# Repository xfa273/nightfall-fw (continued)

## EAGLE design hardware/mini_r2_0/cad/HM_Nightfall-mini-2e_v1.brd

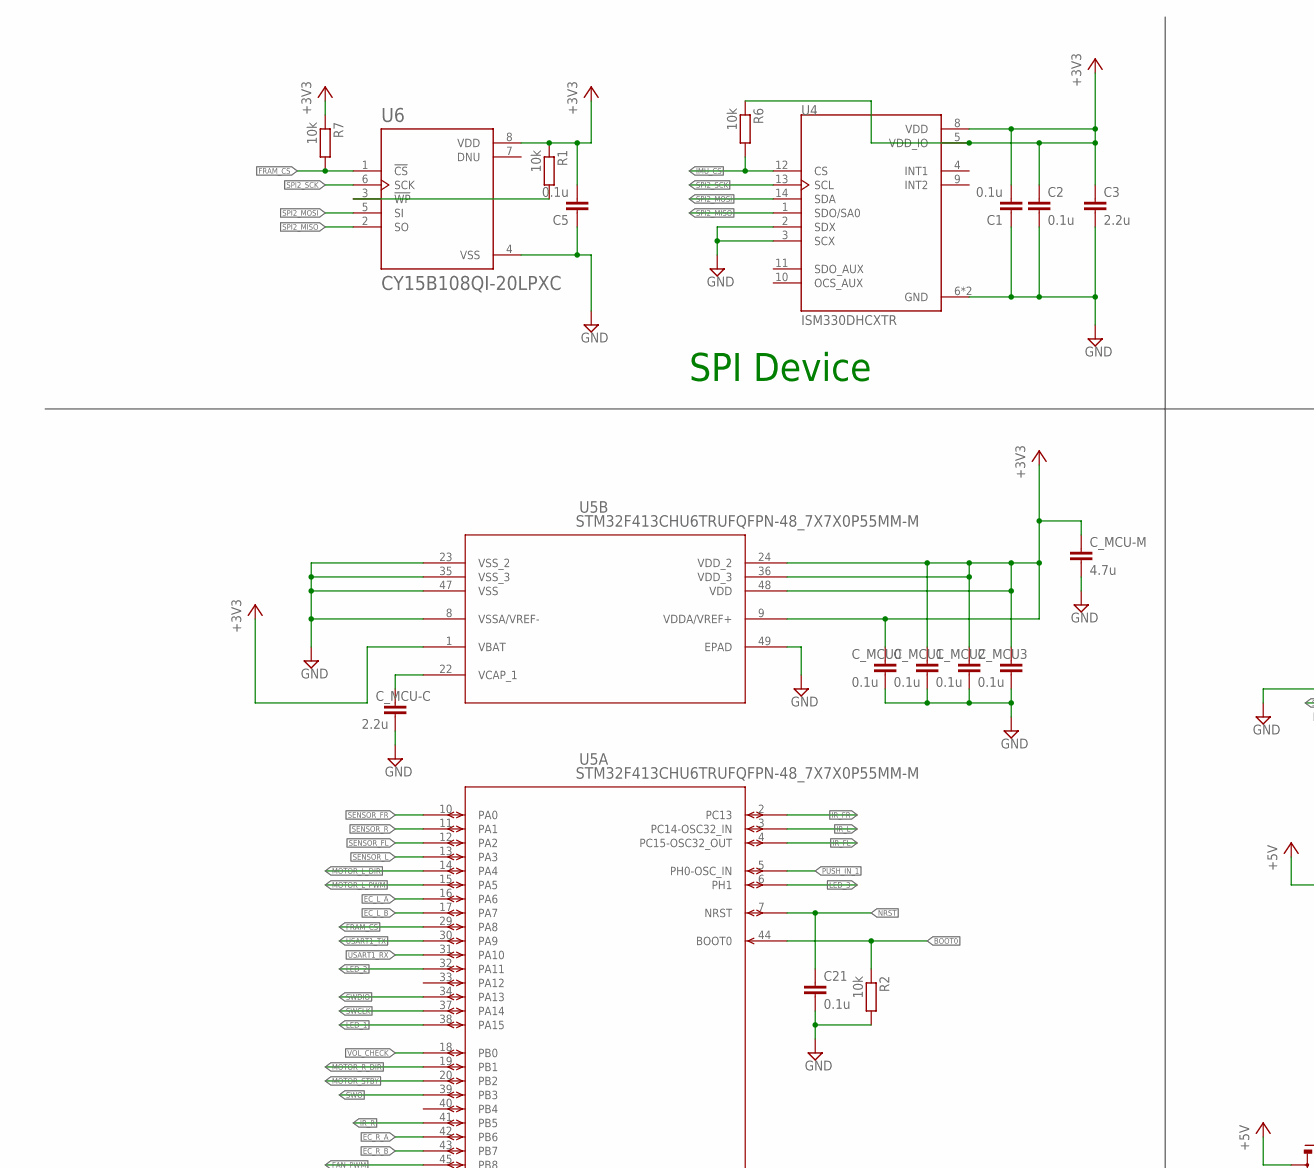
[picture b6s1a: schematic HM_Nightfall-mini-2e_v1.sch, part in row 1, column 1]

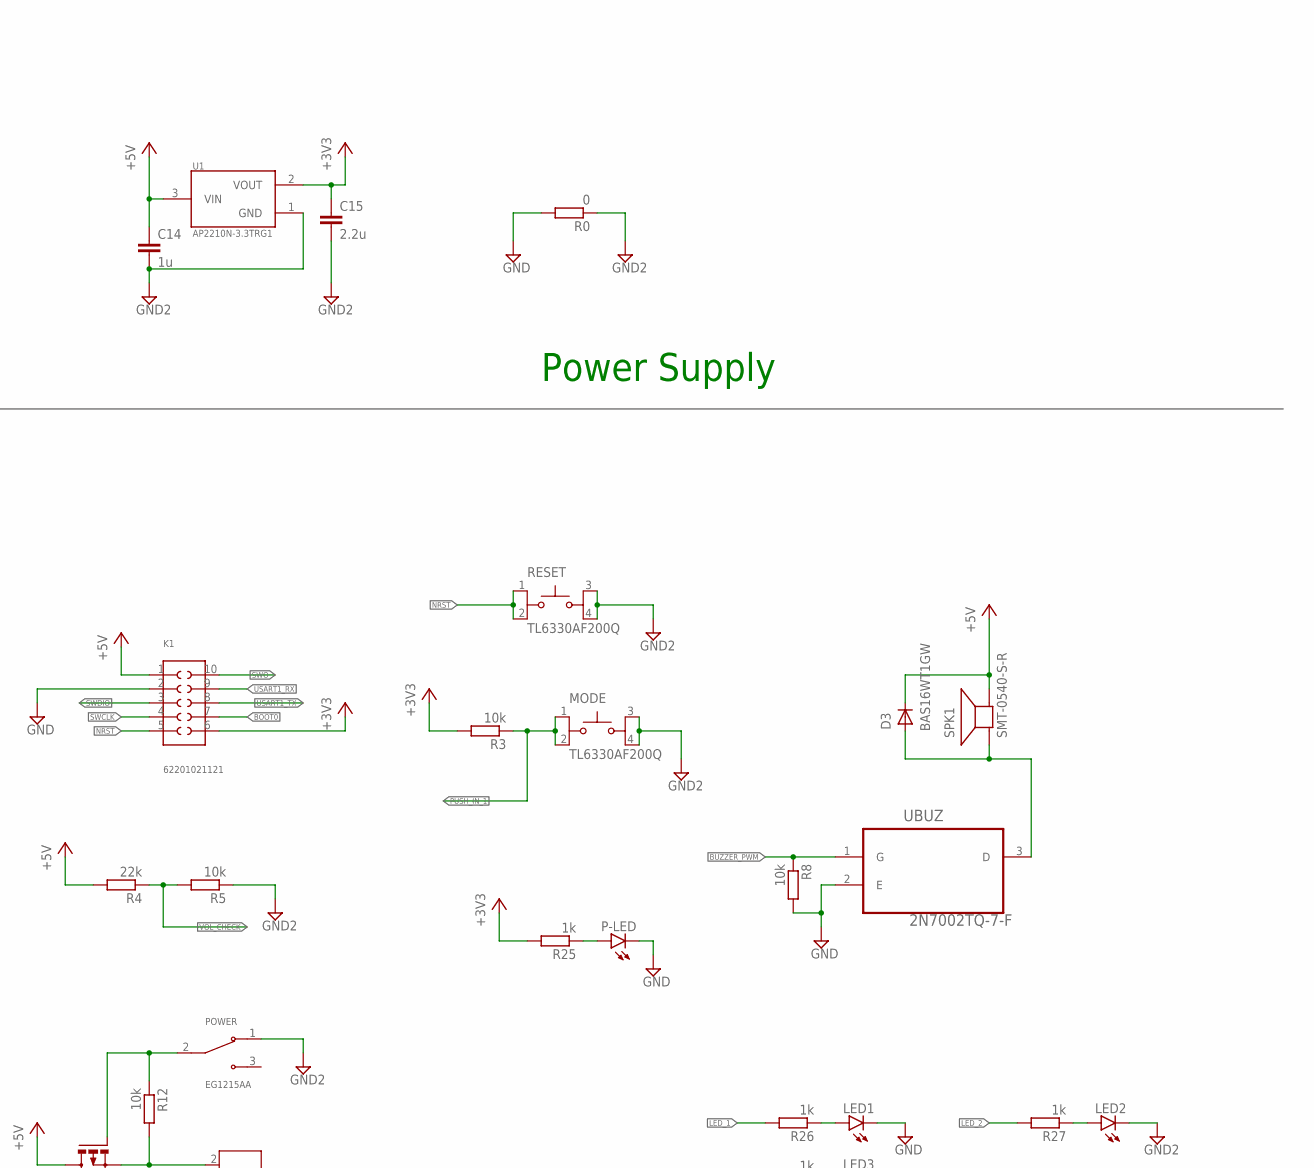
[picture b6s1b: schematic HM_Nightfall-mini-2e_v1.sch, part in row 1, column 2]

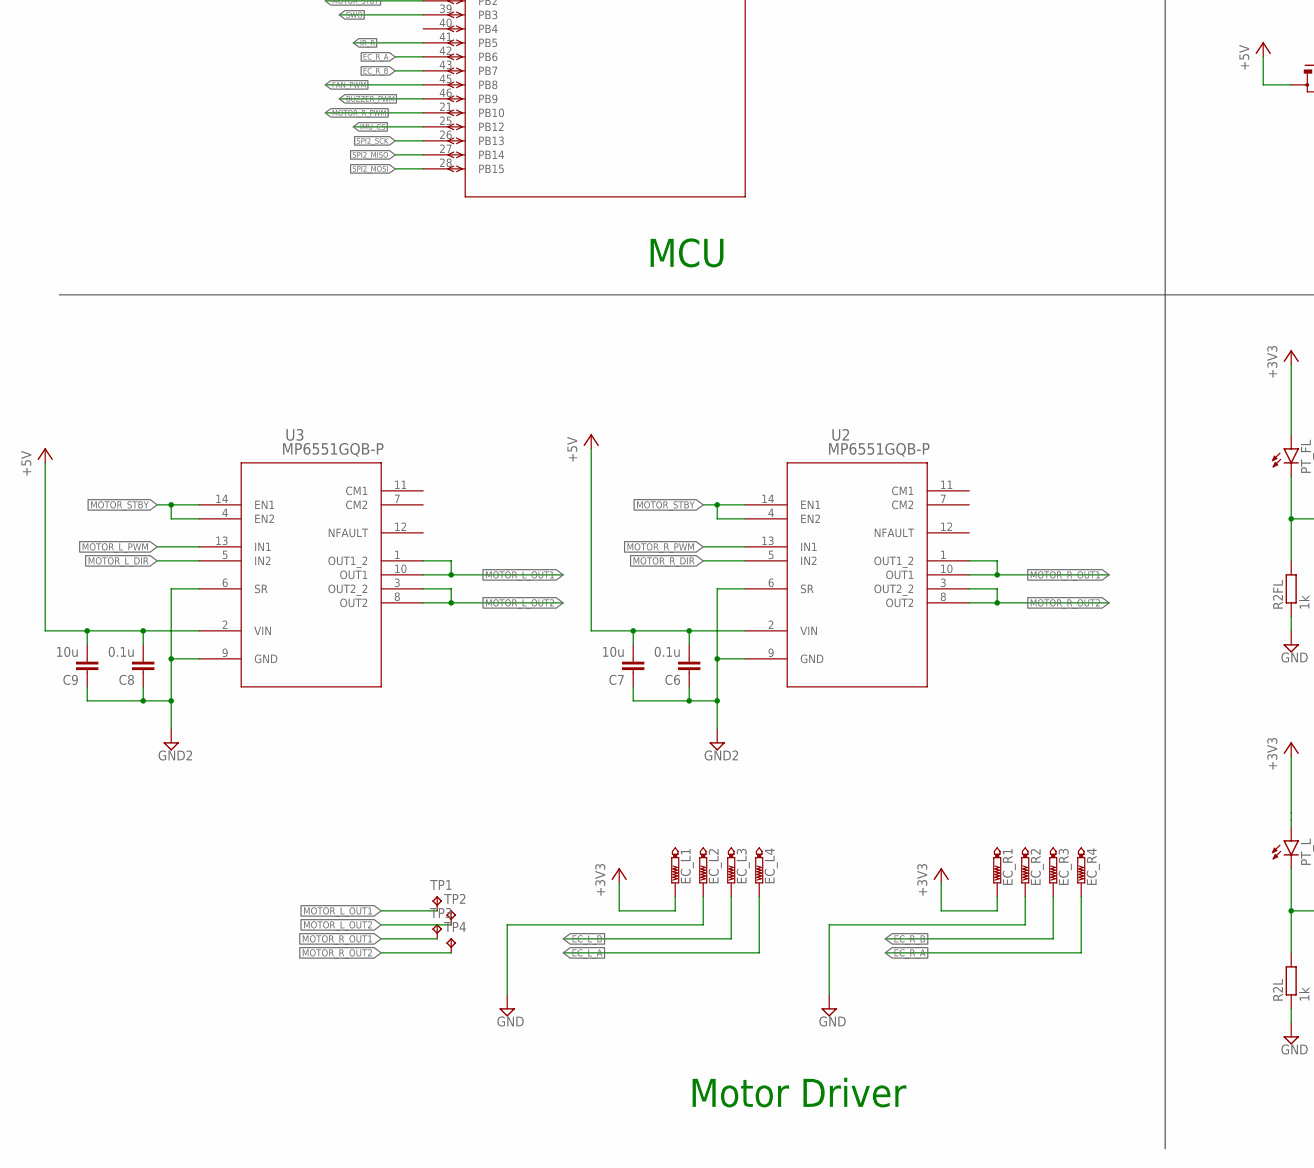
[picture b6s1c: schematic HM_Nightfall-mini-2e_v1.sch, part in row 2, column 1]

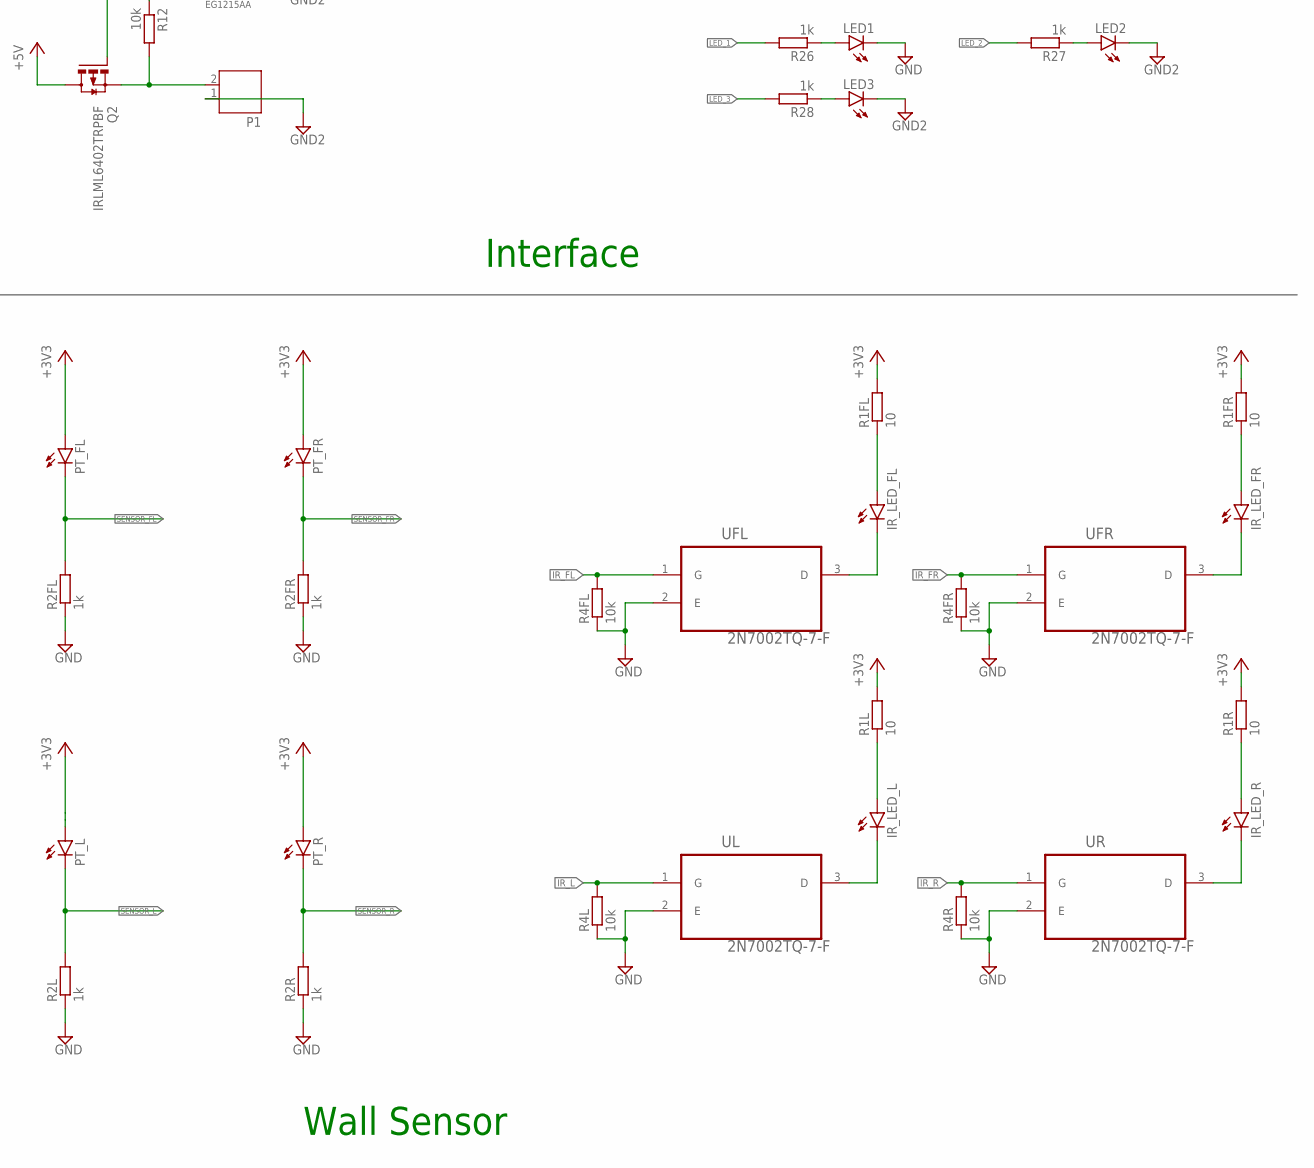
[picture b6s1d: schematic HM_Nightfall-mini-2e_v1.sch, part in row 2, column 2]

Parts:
C1, C2, C5, C6, C8, C21: 0.1u; C0402
C3, C15: 2.2u; C0402
C7, C9: 10u; C0402
C14: 1u; C0402
C_MCU0, C_MCU1, C_MCU2, C_MCU3: 0.1u; C0402
C_MCU-C: 2.2u; C0402
C_MCU-M: 4.7u; C0402
D3: BAS16WT1GW; SOT323
EC_L1, EC_L2, EC_L3, EC_L4: PTR1TP06SQ; TP06SQ
EC_R1, EC_R2, EC_R3, EC_R4: PTR1TP06SQ; TP06SQ
IR_LED_FL: LED3MM
IR_LED_FR: LED3MM
IR_LED_L: LED3MM
IR_LED_R: LED3MM
K1: 62201021121
LED1, LED2, LED3: LEDCHIPLED_0603; CHIPLED_0603
MODE: TL6330AF200Q; SW_TL6330AF200Q
P1: JST-PH2
P-LED: LEDCHIPLED_0603; CHIPLED_0603
POWER: EG1215AA; SW_EG1215AA
PT_FL: LED3MM
PT_FR: LED3MM
PT_L: LED3MM
PT_R: LED3MM
Q2: IRLML6402TRPBF; SOT23
R0: 0; R0402
R1, R2, R3, R4FL, R4FR, R4L, R4R, R5, R6, R7, R8, R12: 10k; R0402
R1FL, R1FR, R1L, R1R: 10; R0402
R2FL, R2FR, R2L, R2R, R25, R26, R27, R28: 1k; R0402
R4: 22k; R0402
RESET: TL6330AF200Q; SW_TL6330AF200Q
SPK1: SMT-0540-S-R
TP1, TP2, TP3, TP4: TPB1,27; B1,27
U1: AP2210N-3.3TRG1; SOT95P280X145-3N
U2, U3: MP6551GQB-P; QFN-14_MP6551_MNP
U4: ISM330DHCXTR; PQFN50P250X300X86-14N
U5: STM32F413CHU6TRUFQFPN-48_7X7X0P55MM-M; UFQFPN-48_7X7X0P55MM-M
U6: CY15B108QI-20LPXC; SON65P328X323X55-8N
UBUZ: 2N7002TQ-7-F; SOT50P160X90-3N
UFL: 2N7002TQ-7-F; SOT50P160X90-3N
UFR: 2N7002TQ-7-F; SOT50P160X90-3N
UL: 2N7002TQ-7-F; SOT50P160X90-3N
UR: 2N7002TQ-7-F; SOT50P160X90-3N

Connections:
+3V3: C1.2, C2.1, C3.1, C5.2, C15.1, C_MCU0.1, C_MCU1.1, C_MCU2.1, C_MCU3.1, C_MCU-M.1, EC_L1.TP, EC_R1.TP, K1.6, PT_FL.A, PT_FR.A, PT_L.A, PT_R.A, R1.1, R1FL.2, R1FR.2, R1L.2, R1R.2, R3.2, R6.1, R7.1, R25.2, U1.2 (VOUT), U4.5 (VDD_IO), U4.8 (VDD), U5.1 (VBAT), U5.9 (VDDA/VREF+), U5.24 (VDD_2), U5.36 (VDD_3), U5.48 (VDD), U6.8 (VDD)
+5V: C6.2, C7.2, C8.2, C9.2, C14.1, D3.3 (K), K1.1, Q2.3 (D), R4.2, SPK1.+ (-), U1.3 (VIN), U2.2 (VIN), U3.2 (VIN)
BOOT0: K1.7, R2.1, U5.44 (BOOT0)
BUZZER_PWM: R8.1, U5.46 (PB9), UBUZ.1 (G)
EC_L_A: EC_L4.TP, U5.16 (PA6)
EC_L_B: EC_L3.TP, U5.17 (PA7)
EC_R_A: EC_R4.TP, U5.42 (PB6)
EC_R_B: EC_R3.TP, U5.43 (PB7)
FAN_PWM: U5.45 (PB8)
FRAM_CS: R7.2, U5.29 (PA8), U6.1 (!CS)
GND: C1.1, C2.2, C3.2, C5.1, C21.2, C_MCU0.2, C_MCU1.2, C_MCU2.2, C_MCU3.2, C_MCU-C.2, C_MCU-M.2, EC_L2.TP, EC_R2.TP, K1.2, LED1.C, P-LED.C, R0.2, R2.2, R2FL.1, R2FR.1, R2L.1, R2R.1, R4FL.1, R4FR.1, R4L.1, R4R.1, R8.2, U4.2 (SDX), U4.3 (SCX), U4.6 (GND), U4.7 (GND), U5.8 (VSSA/VREF-), U5.23 (VSS_2), U5.35 (VSS_3), U5.47 (VSS), U5.49 (EPAD), U6.4 (VSS), UBUZ.2 (E), UFL.2 (E), UFR.2 (E), UL.2 (E), UR.2 (E)
GND2: C6.1, C7.1, C8.1, C9.1, C14.2, C15.2, LED2.C, LED3.C, MODE.3, MODE.4, P1.1, POWER.1, R0.1, R5.1, RESET.3, RESET.4, U1.1 (GND), U2.6 (SR), U2.9 (GND), U3.6 (SR), U3.9 (GND)
IMU_CS: R6.2, U4.12 (CS), U5.25 (PB12)
IR_FL: R4FL.2, U5.4 (PC15-OSC32_OUT), UFL.1 (G)
IR_FR: R4FR.2, U5.2 (PC13), UFR.1 (G)
IR_L: R4L.2, U5.3 (PC14-OSC32_IN), UL.1 (G)
IR_R: R4R.2, U5.41 (PB5), UR.1 (G)
LED_1: R26.2, U5.38 (PA15)
LED_2: R27.2, U5.32 (PA11)
LED_3: R28.2, U5.6 (PH1)
MOTOR_L_DIR: U3.5 (IN2), U5.14 (PA4)
MOTOR_L_OUT1: TP1.TP, U3.1 (OUT1_2), U3.10 (OUT1)
MOTOR_L_OUT2: TP2.TP, U3.3 (OUT2_2), U3.8 (OUT2)
MOTOR_L_PWM: U3.13 (IN1), U5.15 (PA5)
MOTOR_R_DIR: U2.5 (IN2), U5.19 (PB1)
MOTOR_R_OUT1: TP3.TP, U2.1 (OUT1_2), U2.10 (OUT1)
MOTOR_R_OUT2: TP4.TP, U2.3 (OUT2_2), U2.8 (OUT2)
MOTOR_R_PWM: U2.13 (IN1), U5.21 (PB10)
MOTOR_STBY: U2.4 (EN2), U2.14 (EN1), U3.4 (EN2), U3.14 (EN1), U5.20 (PB2)
unnamed: IR_LED_FL.K (C), UFL.3 (D)
unnamed: R1.2, U6.3 (!WP)
unnamed: C_MCU-C.1, U5.22 (VCAP_1)
unnamed: P1.2, Q2.2 (S), R12.2
unnamed: IR_LED_FL.A, R1FL.1
unnamed: IR_LED_L.K (C), UL.3 (D)
unnamed: POWER.2, Q2.1 (G), R12.1
unnamed: IR_LED_L.A, R1L.1
unnamed: IR_LED_FR.K (C), UFR.3 (D)
unnamed: P-LED.A, R25.1
unnamed: D3.1 (A), SPK1.- (+), UBUZ.3 (D)
unnamed: LED1.A, R26.1
unnamed: IR_LED_FR.A, R1FR.1
unnamed: IR_LED_R.K (C), UR.3 (D)
unnamed: IR_LED_R.A, R1R.1
unnamed: LED2.A, R27.1
unnamed: LED3.A, R28.1
NRST: C21.1, K1.5, RESET.1, RESET.2, U5.7 (NRST)
PUSH_IN_1: MODE.1, MODE.2, R3.1, U5.5 (PH0-OSC_IN)
SENSOR_FL: PT_FL.K (C), R2FL.2, U5.12 (PA2)
SENSOR_FR: PT_FR.K (C), R2FR.2, U5.10 (PA0)
SENSOR_L: PT_L.K (C), R2L.2, U5.13 (PA3)
SENSOR_R: PT_R.K (C), R2R.2, U5.11 (PA1)
SPI2_MISO: U4.1 (SDO/SA0), U5.27 (PB14), U6.2 (SO)
SPI2_MOSI: U4.14 (SDA), U5.28 (PB15), U6.5 (SI)
SPI2_SCK: U4.13 (SCL), U5.26 (PB13), U6.6 (SCK)
SWCLK: K1.4, U5.37 (PA14)
SWDIO: K1.3, U5.34 (PA13)
SWO: K1.10, U5.39 (PB3)
USART1_RX: K1.9, U5.31 (PA10)
USART1_TX: K1.8, U5.30 (PA9)
VOL_CHECK: R4.1, R5.2, U5.18 (PB0)

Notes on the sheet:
Power Supply
MCU
Interface
Motor Driver
Wall Sensor
SPI Device

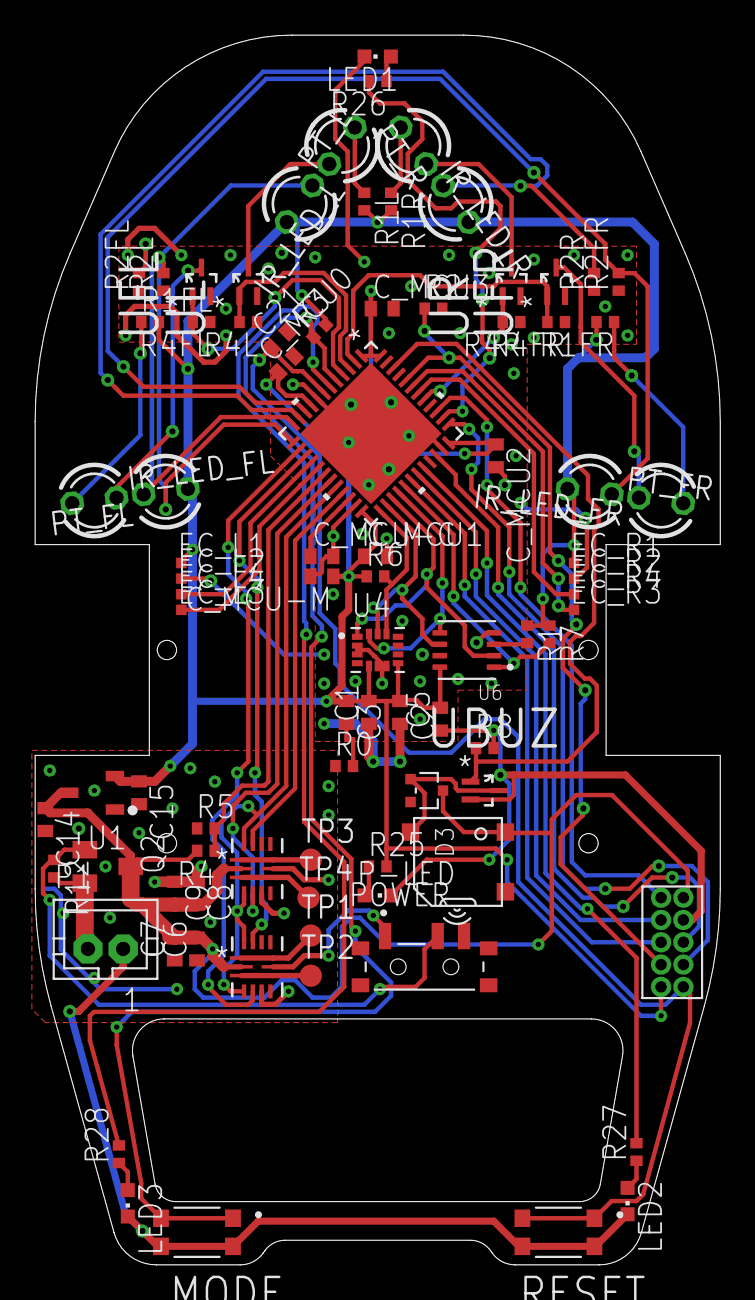
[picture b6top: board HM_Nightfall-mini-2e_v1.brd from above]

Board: 2 copper layers, 39.0 x 70.0 mm, 86 parts (0 on the bottom side), 60 nets.

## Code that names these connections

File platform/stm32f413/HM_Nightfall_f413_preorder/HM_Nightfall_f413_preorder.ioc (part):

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Mcu.Name=STM32F413C(G-H)Ux
Mcu.Package=UFQFPN48
Mcu.UserName=STM32F413CHUx
PA0.GPIOParameters=GPIO_Label
PA0.GPIO_Label=SENSOR_FR
PA0.Signal=ADCx_IN0
PA1.GPIOParameters=GPIO_Label
PA1.GPIO_Label=SENSOR_R
PA1.Signal=ADCx_IN1
PA10.Mode=Asynchronous
PA10.Signal=USART1_RX
PA11.GPIOParameters=GPIO_Label
PA11.GPIO_Label=LED_2
PA11.Signal=GPIO_Output
PA13.Mode=Trace_Asynchronous_SW
PA13.Signal=SYS_JTMS-SWDIO
PA14.Mode=Trace_Asynchronous_SW
PA14.Signal=SYS_JTCK-SWCLK
PA15.GPIOParameters=GPIO_Label
PA15.GPIO_Label=LED_1
PA15.Signal=GPIO_Output
PA2.GPIOParameters=GPIO_Label
PA2.GPIO_Label=SENSOR_FL
PA2.Signal=ADCx_IN2
PA3.GPIOParameters=GPIO_Label
PA3.GPIO_Label=SENSOR_L
PA3.Signal=ADCx_IN3
PA4.GPIOParameters=GPIO_Label
PA4.GPIO_Label=MOTOR_L_DIR
PA4.Signal=GPIO_Output
PA5.GPIOParameters=GPIO_Label
PA5.GPIO_Label=MOTOR_L_PWM
PA5.Signal=S_TIM2_CH1_ETR
PA6.GPIOParameters=GPIO_Label
PA6.GPIO_Label=EC_L_A
PA6.Signal=S_TIM3_CH1
PA7.GPIOParameters=GPIO_Label
PA7.GPIO_Label=EC_L_B
PA7.Signal=S_TIM3_CH2
PA8.GPIOParameters=GPIO_Label
PA8.GPIO_Label=FRAM_CS
PA8.Signal=GPIO_Output
PA9.Mode=Asynchronous
PA9.Signal=USART1_TX
PB0.GPIOParameters=GPIO_Label
PB0.GPIO_Label=VOL_CHECK
PB0.Signal=ADCx_IN8
PB1.GPIOParameters=GPIO_Label
PB1.GPIO_Label=MOTOR_R_DIR
PB1.Signal=GPIO_Output
PB10.GPIOParameters=GPIO_Label
PB10.GPIO_Label=MOTOR_R_PWM
PB10.Signal=S_TIM2_CH3
PB12.GPIOParameters=GPIO_Label
PB12.GPIO_Label=IMU_CS
PB12.Signal=GPIO_Output
PB13.Mode=Full_Duplex_Master
PB13.Signal=SPI2_SCK
PB14.Mode=Full_Duplex_Master
PB14.Signal=SPI2_MISO
PB15.Mode=Full_Duplex_Master
PB15.Signal=SPI2_MOSI
PB2.GPIOParameters=GPIO_Label
PB2.GPIO_Label=MOTOR_STBY
PB2.Signal=GPIO_Output
PB3.Mode=Trace_Asynchronous_SW
PB3.Signal=SYS_JTDO-SWO
PB5.GPIOParameters=GPIO_Label
PB5.GPIO_Label=IR_R
PB5.Signal=GPIO_Output
PB6.GPIOParameters=GPIO_Label
PB6.GPIO_Label=EC_R_A
PB6.Signal=S_TIM4_CH1
PB7.GPIOParameters=GPIO_Label
PB7.GPIO_Label=EC_R_B
PB7.Signal=S_TIM4_CH2
PB8.GPIOParameters=GPIO_Label
PB8.GPIO_Label=FAN_PWM
PB8.Signal=S_TIM10_CH1
PB9.GPIOParameters=GPIO_Label
PB9.GPIO_Label=BUZZER_PWM
PB9.Signal=S_TIM11_CH1
PC13.GPIOParameters=GPIO_Label
PC13.GPIO_Label=IR_FR
PC13.Signal=GPIO_Output
PC14-OSC32_IN.GPIOParameters=GPIO_Label
PC14-OSC32_IN.GPIO_Label=IR_L
PC14-OSC32_IN.Signal=GPIO_Output
PC15-OSC32_OUT.GPIOParameters=GPIO_Label
PC15-OSC32_OUT.GPIO_Label=IR_FL
PC15-OSC32_OUT.Signal=GPIO_Output
PH0\ -\ OSC_IN.GPIOParameters=GPIO_Label
PH0\ -\ OSC_IN.GPIO_Label=PUSH_IN_1
PH0\ -\ OSC_IN.Signal=GPIO_Input
PH1\ -\ OSC_OUT.GPIOParameters=GPIO_Label
PH1\ -\ OSC_OUT.GPIO_Label=LED_3
PH1\ -\ OSC_OUT.Signal=GPIO_Output
RCC.SYSCLKFreq_VALUE=100000000
RCC.SYSCLKSource=RCC_SYSCLKSOURCE_PLLCLK
board=custom

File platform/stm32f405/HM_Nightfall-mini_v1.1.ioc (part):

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Mcu.Name=STM32F405RGTx
Mcu.Package=LQFP64
Mcu.UserName=STM32F405RGTx
PA0-WKUP.GPIOParameters=GPIO_Label
PA0-WKUP.GPIO_Label=SENSOR_FR
PA0-WKUP.Signal=ADCx_IN0
PA1.GPIOParameters=GPIO_Label
PA1.GPIO_Label=SENSOR_R
PA1.Signal=ADCx_IN1
PA10.GPIOParameters=GPIO_Label
PA10.GPIO_Label=PC_TX
PA10.Mode=Asynchronous
PA10.Signal=USART1_RX
PA12.GPIOParameters=GPIO_PuPd,GPIO_Label
PA12.GPIO_Label=IR_FR
PA12.GPIO_PuPd=GPIO_PULLDOWN
PA12.Signal=GPIO_Output
PA13.GPIOParameters=GPIO_Label
PA13.GPIO_Label=SWDIO
PA13.Signal=SYS_JTMS-SWDIO
PA14.GPIOParameters=GPIO_Label
PA14.GPIO_Label=SWCL
PA14.Signal=SYS_JTCK-SWCLK
PA15.GPIOParameters=GPIO_Label
PA15.GPIO_Label=LED_1
PA15.Signal=GPIO_Output
PA2.GPIOParameters=GPIO_Label
PA2.GPIO_Label=SENSOR_FL
PA2.Signal=ADCx_IN2
PA3.GPIOParameters=GPIO_Label
PA3.GPIO_Label=SENSOR_L
PA3.Signal=ADCx_IN3
PA5.GPIOParameters=GPIO_Label
PA5.GPIO_Label=MOTOR_L_PWM
PA5.Signal=S_TIM2_CH1_ETR
PA7.GPIOParameters=GPIO_Label
PA7.GPIO_Label=MOTOR_L_DIR
PA7.Signal=GPIO_Output
PA8.GPIOParameters=GPIO_Label
PA8.GPIO_Label=SCL
PA8.Signal=I2C3_SCL
PA9.GPIOParameters=GPIO_Label
PA9.GPIO_Label=PC_RX
PA9.Mode=Asynchronous
PA9.Signal=USART1_TX
PB10.GPIOParameters=GPIO_Label
PB10.GPIO_Label=MOTOR_R_DIR
PB10.Signal=GPIO_Output
PB11.GPIOParameters=GPIO_Label
PB11.GPIO_Label=MOTOR_R_PWM
PB11.Signal=S_TIM2_CH4
PB15.GPIOParameters=GPIO_Label
PB15.GPIO_Label=LED_2
PB15.Signal=GPIO_Output
PB4.GPIOParameters=GPIO_Label
PB4.GPIO_Label=FAN
PB4.Signal=S_TIM3_CH1
PB5.GPIOParameters=GPIO_Label
PB5.GPIO_Label=BUZZER
PB5.Signal=S_TIM3_CH2
PB6.GPIOParameters=GPIO_Label
PB6.GPIO_Label=EC_L_A
PB6.Signal=S_TIM4_CH1
PB7.GPIOParameters=GPIO_Label
PB7.GPIO_Label=EC_L_B
PB7.Signal=S_TIM4_CH2
PC0.GPIOParameters=GPIO_Label
PC0.GPIO_Label=VOL_CHECK
PC0.Signal=ADCx_IN10
PC1.GPIOParameters=GPIO_Label
PC1.GPIO_Label=PUSH_IN_1
PC1.Signal=GPIO_Input
PC10.GPIOParameters=GPIO_Label
PC10.GPIO_Label=SCK
PC10.Mode=Full_Duplex_Master
PC10.Signal=SPI3_SCK
PC11.GPIOParameters=GPIO_Label
PC11.GPIO_Label=MISO
PC11.Mode=Full_Duplex_Master
PC11.Signal=SPI3_MISO
PC12.GPIOParameters=GPIO_Label
PC12.GPIO_Label=MOSI
PC12.Mode=Full_Duplex_Master
PC12.Signal=SPI3_MOSI
PC13-ANTI_TAMP.GPIOParameters=GPIO_Label
PC13-ANTI_TAMP.GPIO_Label=IR_FL
PC13-ANTI_TAMP.Signal=GPIO_Output
PC14-OSC32_IN.GPIOParameters=GPIO_Label
PC14-OSC32_IN.GPIO_Label=IR_L
PC14-OSC32_IN.Signal=GPIO_Output
PC3.GPIOParameters=GPIO_Label
PC3.GPIO_Label=MOTOR_STBY
PC3.Signal=GPIO_Output
PC6.GPIOParameters=GPIO_Label
PC6.GPIO_Label=EC_R_A
PC6.Signal=S_TIM8_CH1
PC7.GPIOParameters=GPIO_Label
PC7.GPIO_Label=EC_R_B
PC7.Signal=S_TIM8_CH2
PC8.GPIOParameters=GPIO_Label
PC8.GPIO_Label=IR_FR
PC8.Signal=GPIO_Output
PC9.GPIOParameters=GPIO_Label
PC9.GPIO_Label=IR_R
PC9.Signal=GPIO_Output
PD2.GPIOParameters=GPIO_Label
PD2.GPIO_Label=CS
PD2.Signal=GPIO_Output
PH1-OSC_OUT.GPIOParameters=GPIO_Label
PH1-OSC_OUT.GPIO_Label=LED_3
PH1-OSC_OUT.Signal=GPIO_Output
RCC.HSE_VALUE=25000000
RCC.SYSCLKFreq_VALUE=168000000
RCC.SYSCLKSource=RCC_SYSCLKSOURCE_PLLCLK
board=custom

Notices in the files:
parts and their libraries:
pinheader_1m27: Copyright: Würth Elektronik
COPYRIGHT: Copyright (C) 2025 Ultra Librarian. All rights reserved.
COPYRIGHT: Copyright (C) 2026 Ultra Librarian. All rights reserved.
